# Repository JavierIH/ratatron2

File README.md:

<h1 align="center">Ratatron II</h1>

<p align="center">
  Micromouse robot with four-wheel drive and a suction fan.
</p>

<p align="center">

</p>

> **Work in progress.** The board is being routed and the firmware is waiting for it. The picture is the KiCad 3D
> view, not a photo (yet).

## What's inside

| | |
|---|---|
| **MCU** | STM32F446RET6, Cortex-M4F at 180 MHz |
| **Wall sensors** | 4 IR pairs: SFH4550 emitters and ST-1KL3A phototransistors |
| **IMU** | LSM6DSRX (gyro and accelerometer) over SPI |
| **Drive** | 4 wheels, 2 motors, 2 DRV8874 H-bridges at 20 kHz with current sensing |
| **Encoders** | 2 AS5147P, magnetic, on little boards that snap off the main one |
| **Suction** | a fan driven by a coreless motor, over a hole in the middle of the board |
| **Battery** | 2S LiPo |
| **Interface** | 6 blue LEDs, 2 buttons and a power switch |
| **Connectors** | SWD through a magnetic connector, serial on a header |

## Where things are

- [firmware](firmware/): C on libopencm3, built with PlatformIO (`cd firmware && pio run`, flashed with an ST-Link)
- [hardware](hardware/): KiCad 9 schematic, PCB and custom library
- [mechanics](mechanics/): FreeCAD model (wheels, motor and fan supports)

## Family

- [Ratatron](https://github.com/JavierIH/ratatron), the first one
- [Ratasim](https://github.com/JavierIH/ratasim), the simulator

## Licence

- Firmware: GPLv3 ([LICENSE](LICENSE))
- Electronics: CC BY-SA 4.0 ([hardware/LICENSE](hardware/LICENSE))
- Mechanics: CC BY-SA 4.0 ([mechanics/LICENSE](mechanics/LICENSE))

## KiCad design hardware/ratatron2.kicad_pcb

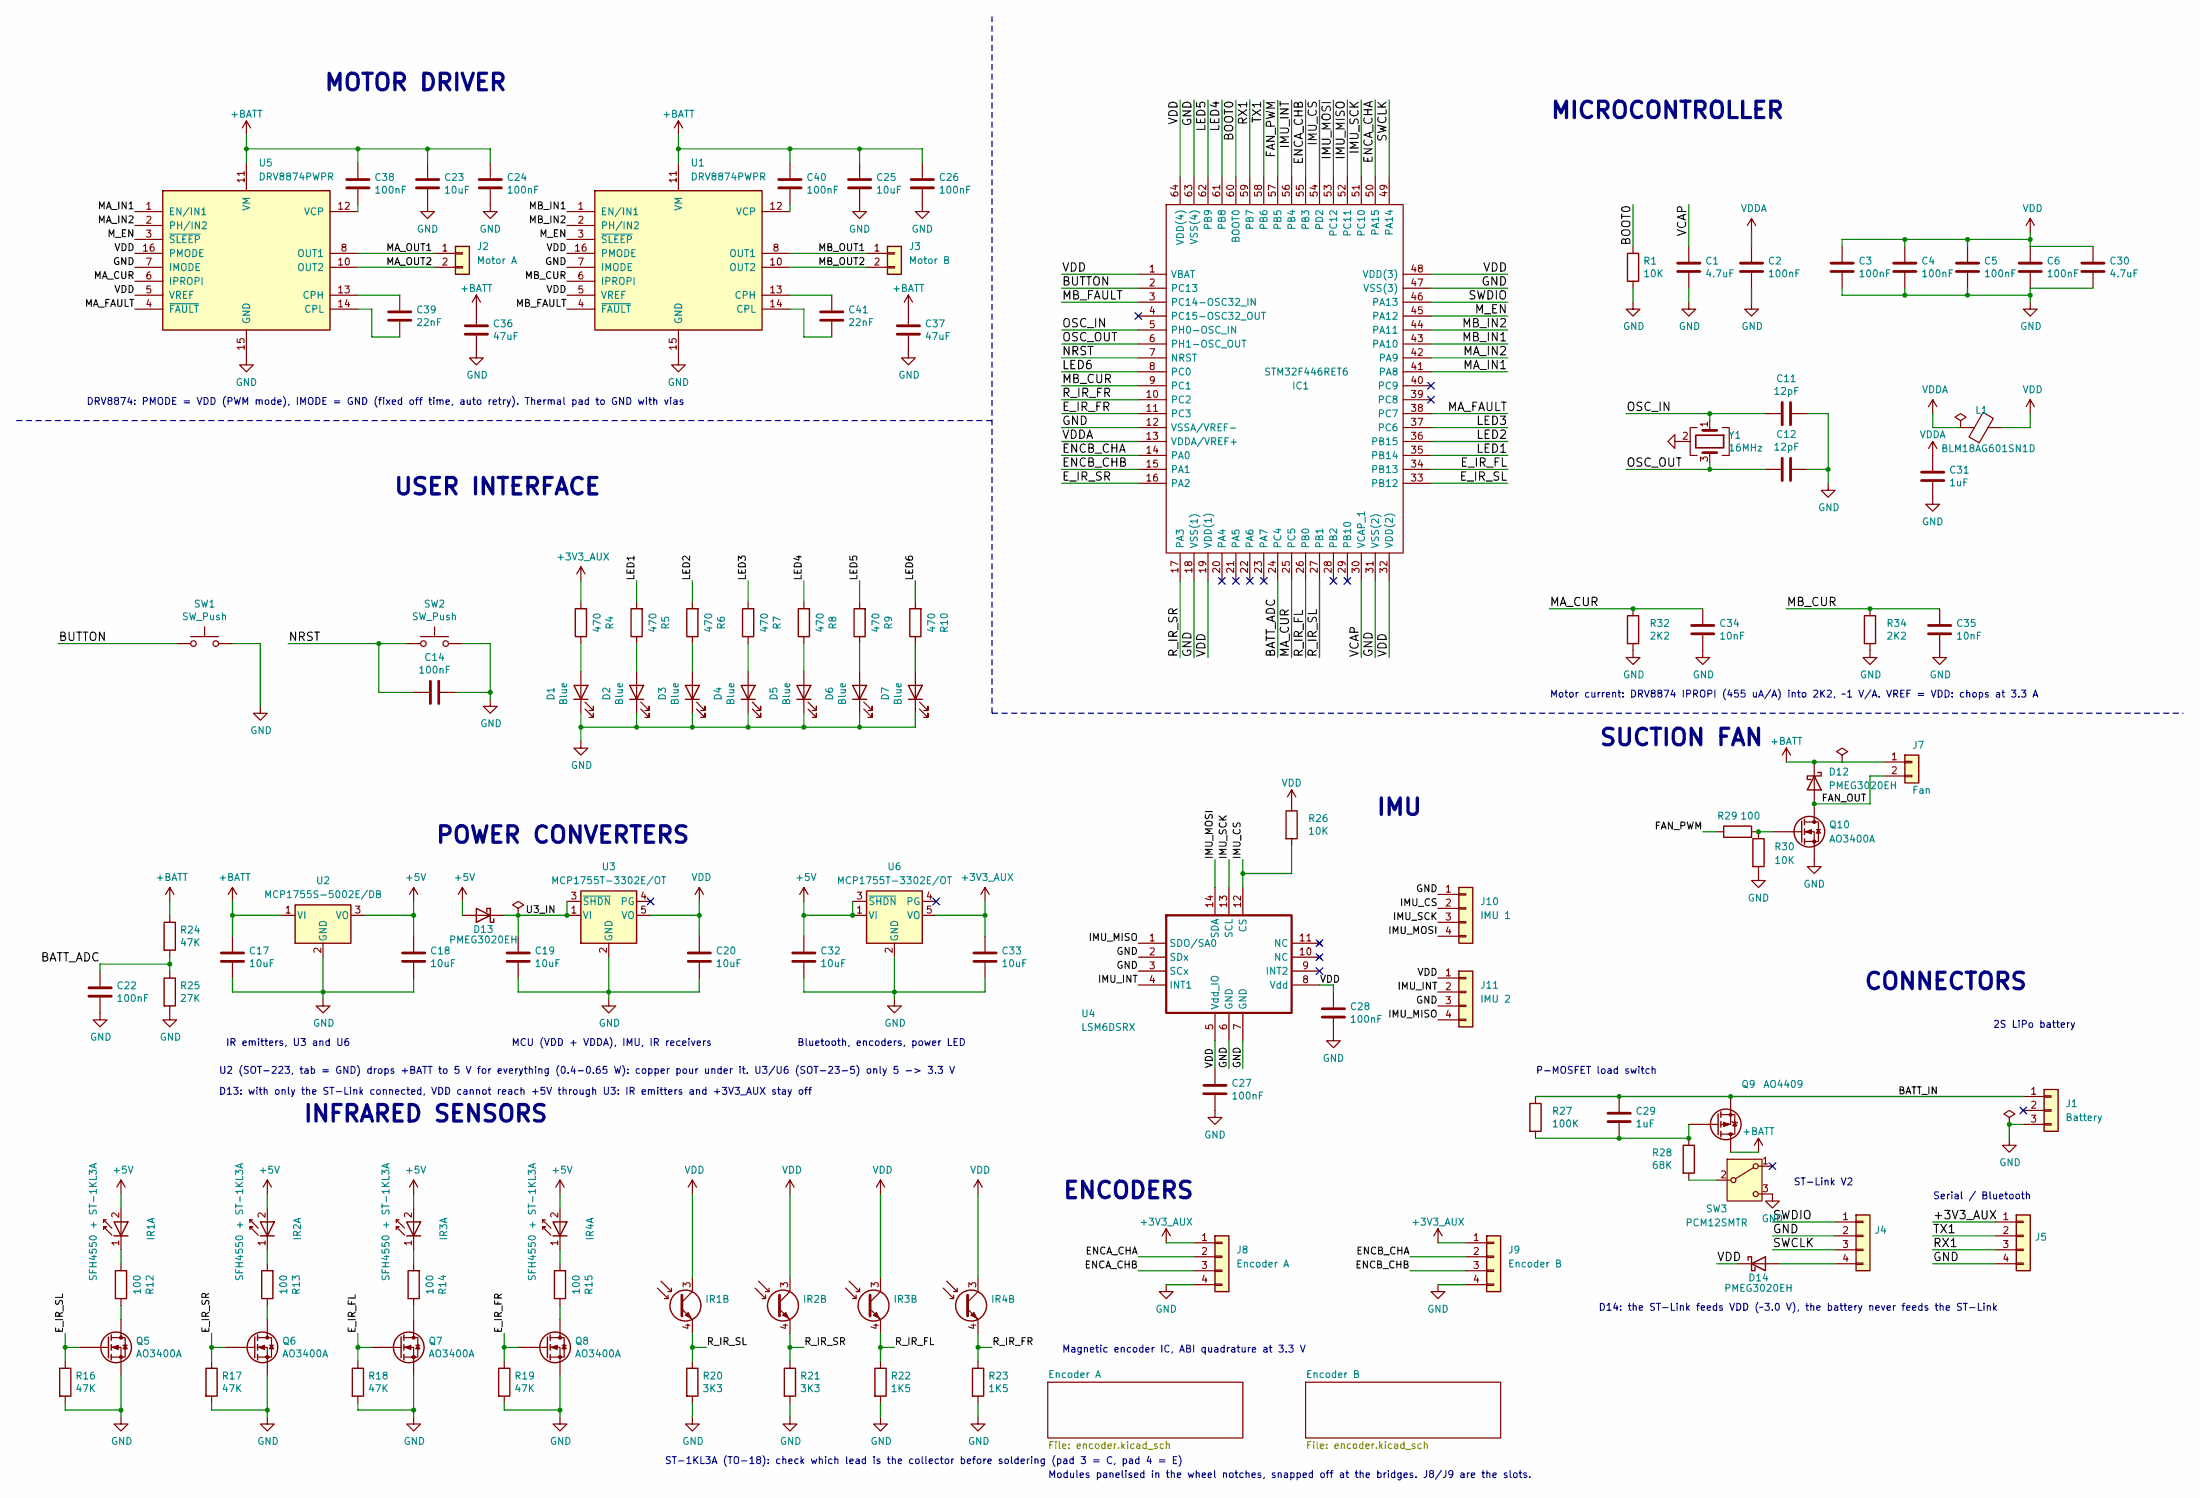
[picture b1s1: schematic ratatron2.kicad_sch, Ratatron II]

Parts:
C1, C30: 4.7uF; R_0603_1608Metric
C2, C3, C4, C5, C6, C14, C22, C24, C26, C27, C28, C38, C40: 100nF; R_0603_1608Metric
C11, C12: 12pF; R_0603_1608Metric
C17, C18, C19, C20, C23, C25, C32, C33: 10uF; R_0603_1608Metric
C29, C31: 1uF; R_0603_1608Metric
C34, C35: 10nF; R_0603_1608Metric
C36, C37: 47uF; C_1206_3216Metric
C39, C41: 22nF; R_0603_1608Metric
D1, D2, D3, D4, D5, D6, D7: Blue; D_0603_1608Metric
D12, D13, D14: PMEG3020EH; D_SOD-123F
IC1: STM32F446RET6; LQFP-64_10x10mm_P0.5mm; Manufacturer_Part_Number STM32F446RET6
IR1, IR3: SFH4550 + ST-1KL3A; IR_PAIR_1x04
IR2, IR4: SFH4550 + ST-1KL3A; IR_PAIR_1x04_R
J1: Battery; JST_XH_B3B-XH-A_1x03_P2.50mm_Vertical
J2: Motor A; SolderPads_1x02_P2.54mm
J3: Motor B; SolderPads_1x02_P2.54mm
J4: SWD; Conn_Magnetic_1x04_P2.54mm_Horizontal
J5: Serial; PinSocket_1x04_P2.54mm_Vertical
J7: Fan; SolderPads_1x02_P2.00mm
J8: Encoder A; Encoder_Slot_1x04
J9: Encoder B; Encoder_Slot_1x04
J10: IMU 1; PinHeader_1x04_P1.27mm_IMU
J11: IMU 2; PinHeader_1x04_P1.27mm_IMU
L1: BLM18AG601SN1D; R_0603_1608Metric
Q5, Q6, Q7, Q8, Q10: AO3400A; SOT-23
Q9: AO4409; SOIC-8_3.9x4.9mm_P1.27mm
R1, R26, R30: 10K; R_0603_1608Metric
R4, R5, R6, R7, R8, R9, R10: 470; R_0603_1608Metric
R12, R13, R14, R15, R29: 100; R_0603_1608Metric
R16, R17, R18, R19, R24: 47K; R_0603_1608Metric
R20, R21: 3K3; R_0603_1608Metric
R22, R23: 1K5; R_0603_1608Metric
R25: 27K; R_0603_1608Metric
R27: 100K; R_0603_1608Metric
R28: 68K; R_0603_1608Metric
R32, R34: 2K2; R_0603_1608Metric
SW1, SW2: SW_Push; SW_Push_1P1T_NO_CK_KMR2
SW3: PCM12SMTR; SW_SPDT_PCM12
U1, U5: DRV8874PWPR; HTSSOP-16-1EP_4.4x5mm_P0.65mm_EP3.4x5mm_Mask2.46x3.55mm
U2: MCP1755S-5002E/DB; SOT-223-3_TabPin2
U3, U6: MCP1755T-3302E/OT; SOT-23-5
U4: LSM6DSRX; Bosch_LGA-14_3x2.5mm_P0.5mm
Y1: 16MHz; Crystal_SMD_3225-4Pin_3.2x2.5mm

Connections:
+3V3_AUX: C33.1, J5.1, J8.1, J9.1, R4.2, U6.5 (VO)
+5V: C18.1, C32.1, D13.2 (A), IR1.2 (A), IR2.2 (A), IR3.2 (A), IR4.2 (A), U2.3 (VO), U6.1 (VI), U6.3 (~SHDN)
+BATT: C17.1, C23.1, C24.1, C25.1, C26.1, C36.1, C37.1, C38.1, C40.1, D12.1 (K), J7.1, Q9.5 (D), Q9.6 (D), Q9.7 (D), Q9.8 (D), R24.1, U1.11 (VM), U2.1 (VI), U5.11 (VM)
/BATT_ADC: C22.1, IC1.24 (PC4), R24.2, R25.1
/BATT_IN: C29.1, J1.1, Q9.1 (S), Q9.2 (S), Q9.3 (S), R27.1
/BOOT0: IC1.60 (BOOT0), R1.1
/BUTTON: IC1.2 (PC13), SW1.1; also elsewhere on the board
/ENCA_CHA: IC1.50 (PA15), J8.2
/ENCA_CHB: IC1.55 (PB3), J8.3
/ENCB_CHA: IC1.14 (PA0), J9.2
/ENCB_CHB: IC1.15 (PA1), J9.3
/E_IR_FL: IC1.34 (PB13), Q7.1 (G), R18.1
/E_IR_FR: IC1.11 (PC3), Q8.1 (G), R19.1
/E_IR_SL: IC1.33 (PB12), Q5.1 (G), R16.1
/E_IR_SR: IC1.16 (PA2), Q6.1 (G), R17.1
/FAN_OUT: D12.2 (A), J7.2, Q10.3 (D)
/FAN_PWM: IC1.57 (PB5), R29.1
/IMU_CS: IC1.54 (PD2), J10.2, R26.2, U4.12 (CS)
/IMU_INT: IC1.56 (PB4), J11.2, U4.4 (INT1)
/IMU_MISO: IC1.52 (PC11), J11.4, U4.1 (SDO/SA0)
/IMU_MOSI: IC1.53 (PC12), J10.4, U4.14 (SDA)
/IMU_SCK: IC1.51 (PC10), J10.3, U4.13 (SCL)
/LED1: IC1.35 (PB14), R5.2
/LED2: IC1.36 (PB15), R6.2
/LED3: IC1.37 (PC6), R7.2
/LED4: IC1.61 (PB8), R8.2
/LED5: IC1.62 (PB9), R9.2
/LED6: IC1.8 (PC0), R10.2
/MA_CUR: C34.1, IC1.25 (PC5), R32.1, U5.6 (IPROPI)
/MA_FAULT: IC1.38 (PC7), U5.4 (~FAULT)
/MA_IN1: IC1.41 (PA8), U5.1 (EN/IN1)
/MA_IN2: IC1.42 (PA9), U5.2 (PH/IN2)
/MA_OUT1: J2.1, U5.8 (OUT1)
/MA_OUT2: J2.2, U5.10 (OUT2)
/MB_CUR: C35.1, IC1.9 (PC1), R34.1, U1.6 (IPROPI)
/MB_FAULT: IC1.3 (PC14-OSC32_IN), U1.4 (~FAULT)
/MB_IN1: IC1.43 (PA10), U1.1 (EN/IN1)
/MB_IN2: IC1.44 (PA11), U1.2 (PH/IN2)
/MB_OUT1: J3.1, U1.8 (OUT1)
/MB_OUT2: J3.2, U1.10 (OUT2)
/M_EN: IC1.45 (PA12), U1.3 (~SLEEP), U5.3 (~SLEEP)
/NRST: C14.2, IC1.7 (NRST), SW2.1; also elsewhere on the board
/OSC_IN: C11.2, IC1.5 (PH0-OSC_IN), Y1.1
/OSC_OUT: C12.2, IC1.6 (PH1-OSC_OUT), Y1.3
/RX1: IC1.59 (PB7), J5.3
/R_IR_FL: IC1.26 (PB0), IR3.4 (E), R22.1
/R_IR_FR: IC1.10 (PC2), IR4.4 (E), R23.1
/R_IR_SL: IC1.27 (PB1), IR1.4 (E), R20.1
/R_IR_SR: IC1.17 (PA3), IR2.4 (E), R21.1
/SWCLK: IC1.49 (PA14), J4.3
/SWDIO: IC1.46 (PA13), J4.1
/TX1: IC1.58 (PB6), J5.2
/U3_IN: C19.1, D13.1 (K), U3.1 (VI), U3.3 (~SHDN)
/VCAP: C1.1, IC1.30 (VCAP_1)
GND: C1.2, C2.2, C3.2, C4.2, C5.2, C6.2, C11.1, C12.1, C14.1, C17.2, C18.2, C19.2, C20.2, C22.2, C23.2, C24.2, C25.2, C26.2, C27.2, C28.2, C30.2, C31.2, C32.2, C33.2, C34.2, C35.2, C36.2, C37.2, D1.1 (K), D2.1 (K), D3.1 (K), D4.1 (K), D5.1 (K), D6.1 (K), D7.1 (K), IC1.12 (VSSA/VREF-), IC1.18 (VSS(1)), IC1.31 (VSS(2)), IC1.47 (VSS(3)), IC1.63 (VSS(4)), J1.3, J4.2, J5.4, J8.4, J9.4, J10.1, J11.3, Q5.2 (S), Q6.2 (S), Q7.2 (S), Q8.2 (S), Q10.2 (S), R1.2, R16.2, R17.2, R18.2, R19.2, R20.2, R21.2, R22.2, R23.2, R25.2, R30.2, R32.2, R34.2, SW1.2, SW2.2, SW3.3 (C), U1.7 (IMODE), U1.9 (PGND), U1.15 (GND), U1.17 (PAD), U2.2 (GND), U3.2 (GND), U4.2 (SDx), U4.3 (SCx), U4.6 (GND), U4.7 (GND), U5.7 (IMODE), U5.9 (PGND), U5.15 (GND), U5.17 (PAD), U6.2 (GND), Y1.2 (G), Y1.4 (G); also elsewhere on the board
unnamed: D1.2 (A), R4.1
unnamed: D2.2 (A), R5.1
unnamed: D3.2 (A), R6.1
unnamed: D4.2 (A), R7.1
unnamed: D5.2 (A), R8.1
unnamed: D6.2 (A), R9.1
unnamed: D7.2 (A), R10.1
unnamed: D14.2 (A), J4.4
unnamed: IR1.1 (K), R12.2
unnamed: IR2.1 (K), R13.2
unnamed: IR3.1 (K), R14.2
unnamed: IR4.1 (K), R15.2
unnamed: Q5.3 (D), R12.1
unnamed: Q6.3 (D), R13.1
unnamed: Q7.3 (D), R14.1
unnamed: Q8.3 (D), R15.1
unnamed: C29.2, Q9.4 (G), R27.2, R28.1
unnamed: Q10.1 (G), R29.2, R30.1
unnamed: R28.2, SW3.2 (B)
unnamed: C41.1, U1.13 (CPH)
unnamed: C41.2, U1.14 (CPL)
unnamed: C40.2, U1.12 (VCP)
unnamed: C39.1, U5.13 (CPH)
unnamed: C39.2, U5.14 (CPL)
unnamed: C38.2, U5.12 (VCP)
VDD: C3.1, C4.1, C5.1, C6.1, C20.1, C27.1, C28.1, C30.1, D14.1 (K), IC1.1 (VBAT), IC1.19 (VDD(1)), IC1.32 (VDD(2)), IC1.48 (VDD(3)), IC1.64 (VDD(4)), IR1.3 (C), IR2.3 (C), IR3.3 (C), IR4.3 (C), J11.1, L1.2, R26.1, U1.5 (VREF), U1.16 (PMODE), U3.5 (VO), U4.5 (Vdd_IO), U4.8 (Vdd), U5.5 (VREF), U5.16 (PMODE)
VDDA: C2.1, C31.1, IC1.13 (VDDA/VREF+), L1.1

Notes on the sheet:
Motor current: DRV8874 IPROPI (455 uA/A) into 2K2, ~1 V/A. VREF = VDD: chops at 3.3 A
ST-1KL3A (TO-18): check which lead is the collector before soldering (pad 3 = C, pad 4 = E)
Magnetic encoder IC, ABI quadrature at 3.3 V
POWER CONVERTERS
DRV8874: PMODE = VDD (PWM mode), IMODE = GND (fixed off time, auto retry). Thermal pad to GND with vias
P-MOSFET load switch
ENCODERS
MOTOR DRIVER
SUCTION FAN
D14: the ST-Link feeds VDD (~3.0 V), the battery never feeds the ST-Link
ST-Link V2
USER INTERFACE
IMU
MCU (VDD + VDDA), IMU, IR receivers
U2 (SOT-223, tab = GND) drops +BATT to 5 V for everything (0.4-0.65 W): copper pour under it. U3/U6 (SOT-23-5) only 5 -> 3.3 V
Serial / Bluetooth
IR emitters, U3 and U6
INFRARED SENSORS
Bluetooth, encoders, power LED
D13: with only the ST-Link connected, VDD cannot reach +5V through U3: IR emitters and +3V3_AUX stay off
2S LiPo battery
MICROCONTROLLER
CONNECTORS
Modules panelised in the wheel notches, snapped off at the bridges. J8/J9 are the slots.

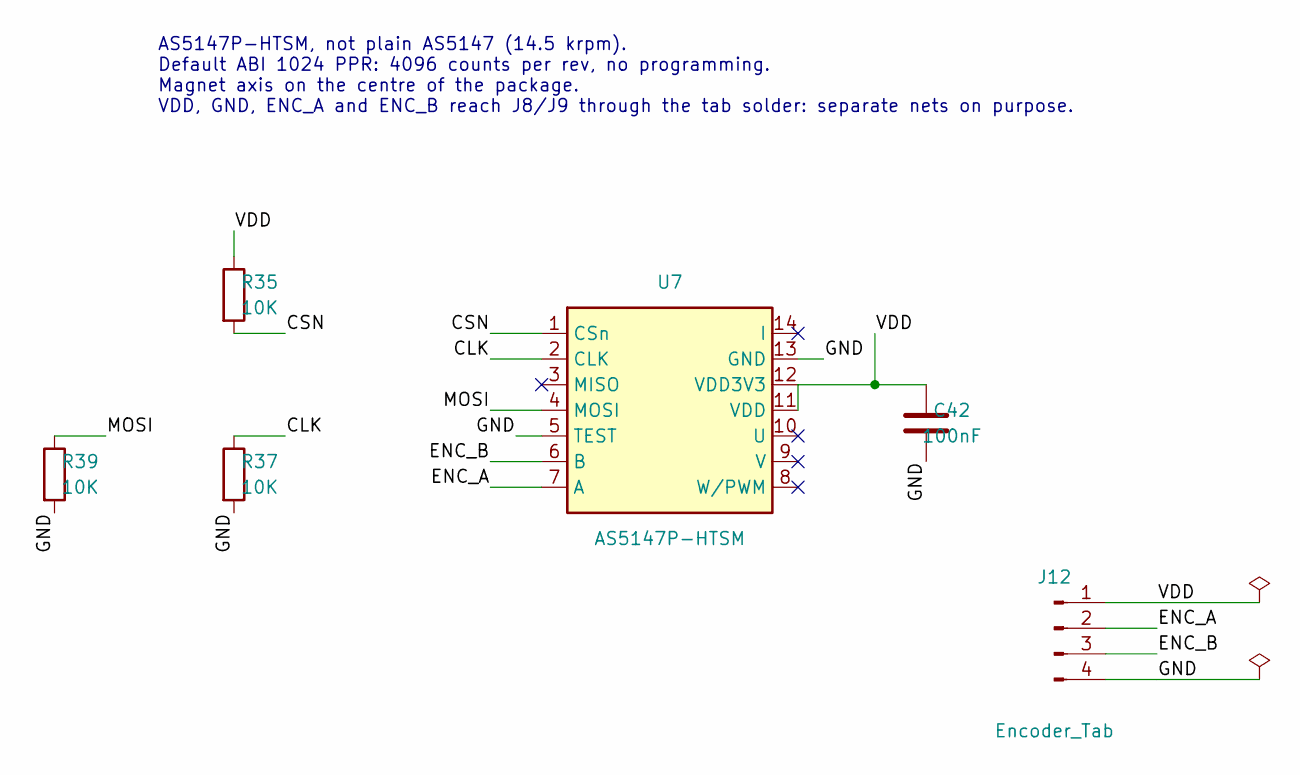
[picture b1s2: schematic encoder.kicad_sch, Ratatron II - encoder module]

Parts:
C42: 100nF; R_0603_1608Metric
J12: Encoder_Tab; Encoder_Tab_1x04
R35, R37, R39: 10K; R_0603_1608Metric
U7: AS5147P-HTSM; TSSOP-14_4.4x5mm_P0.65mm

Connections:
/Encoder A/CLK: R37.1, U7.2 (CLK)
/Encoder A/CSN: R35.2, U7.1 (CSn)
/Encoder A/ENC_A: J12.2, U7.7 (A)
/Encoder A/ENC_B: J12.3, U7.6 (B)
/Encoder A/GND: C42.2, J12.4, R37.2, R39.2, U7.5 (TEST), U7.13 (GND)
/Encoder A/MOSI: R39.1, U7.4 (MOSI)
/Encoder A/VDD: C42.1, J12.1, R35.1, U7.11 (VDD), U7.12 (VDD3V3)

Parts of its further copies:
C43: 100nF; R_0603_1608Metric
J13: Encoder_Tab; Encoder_Tab_1x04
R36, R38, R40: 10K; R_0603_1608Metric
U8: AS5147P-HTSM; TSSOP-14_4.4x5mm_P0.65mm

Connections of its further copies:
/Encoder B/CLK: R38.1, U8.2 (CLK)
/Encoder B/CSN: R36.2, U8.1 (CSn)
/Encoder B/ENC_A: J13.2, U8.7 (A)
/Encoder B/ENC_B: J13.3, U8.6 (B)
/Encoder B/GND: C43.2, J13.4, R38.2, R40.2, U8.5 (TEST), U8.13 (GND)
/Encoder B/MOSI: R40.1, U8.4 (MOSI)
/Encoder B/VDD: C43.1, J13.1, R36.1, U8.11 (VDD), U8.12 (VDD3V3)

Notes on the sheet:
AS5147P-HTSM, not plain AS5147 (14.5 krpm). Default ABI 1024 PPR: 4096 counts per rev, no programming. Magnet axis on the centre of the package. VDD, GND, ENC_A and ENC_B reach J8/J9 through the tab solder: separate nets on purpose.

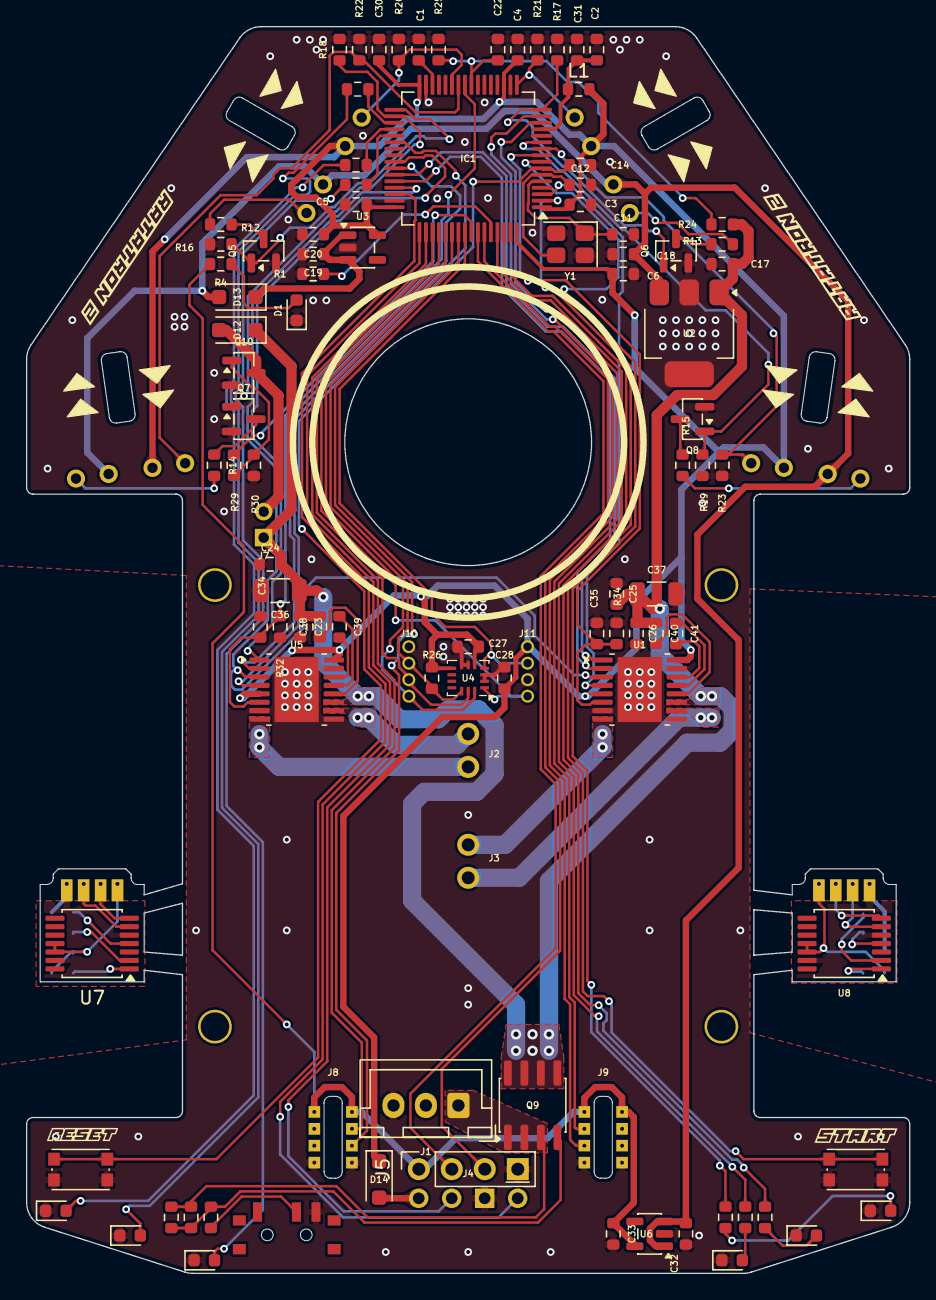
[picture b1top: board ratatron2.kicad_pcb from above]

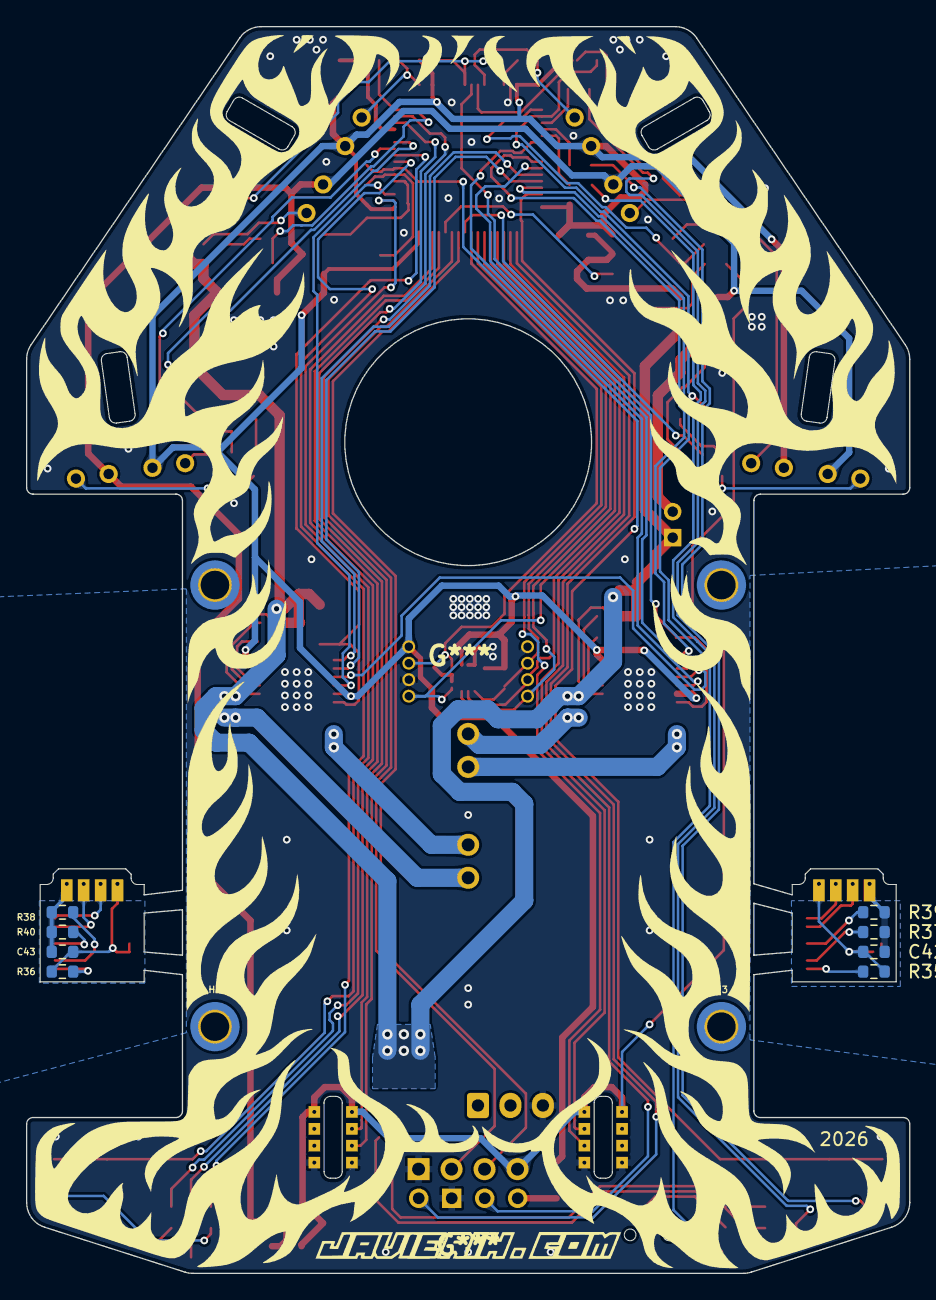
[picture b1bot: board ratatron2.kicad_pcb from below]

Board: 2 copper layers, 68.0 x 96.0 mm, 121 parts (13 on the bottom side), 94 nets.

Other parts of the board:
H1, H2, H3, H4: MountingHole_2.2mm_M2_ISO14580_Pad_TopOnly
MECH1: Drivetrain
RESET: SW_Push; SW_Push_1P1T_NO_CK_KMR2
SELECT: SW_Push; SW_Push_1P1T_NO_CK_KMR2

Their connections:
/BUTTON: SELECT.1; also elsewhere on the board
/NRST: RESET.1; also elsewhere on the board
GND: RESET.2, SELECT.2; also elsewhere on the board

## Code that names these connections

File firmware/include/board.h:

#ifndef BOARD_H
#define BOARD_H

#include <libopencm3/stm32/gpio.h>
#include <libopencm3/stm32/adc.h>

// Ratatron II pinout (STM32F446RET6, LQFP64)
// Net names match hardware/ratatron2.kicad_sch. Pin = LQFP64 package pin.
// IC1 sits at rot 180 in the nose: pins 17-32 face the front edge, 33-48 the
// left IR, 49-64 the fan (rear) and 1-16 the right IR.
//
//  Pin  Port  Net        Function
//   2   PC13  BUTTON     in, internal pull-up, active low
//   3   PC14  MB_FAULT   in, nFAULT of U1
//   5   PH0   OSC_IN     16MHz HSE
//   6   PH1   OSC_OUT
//   8   PC0   LED6       out
//   9   PC1   MB_CUR     ADC123_IN11, IPROPI of U1 (motor B current)
//  10   PC2   R_IR_FR    ADC123_IN12
//  11   PC3   E_IR_FR    out
//  14   PA0   ENCB_CHA   TIM5_CH1 AF2 (32 bit timer)
//  15   PA1   ENCB_CHB   TIM5_CH2 AF2
//  16   PA2   E_IR_SR    out
//  17   PA3   R_IR_SR    ADC123_IN3
//  24   PC4   BATT_ADC   ADC12_IN14
//  25   PC5   MA_CUR     ADC12_IN15, IPROPI of U5 (motor A current)
//  26   PB0   R_IR_FL    ADC12_IN8
//  27   PB1   R_IR_SL    ADC12_IN9
//  33   PB12  E_IR_SL    out
//  34   PB13  E_IR_FL    out
//  35   PB14  LED1       out
//  36   PB15  LED2       out
//  37   PC6   LED3       out
//  38   PC7   MA_FAULT   in, nFAULT of U5
//  41   PA8   MA_IN1     TIM1_CH1 AF1
//  42   PA9   MA_IN2     TIM1_CH2 AF1
//  43   PA10  MB_IN1     TIM1_CH3 AF1
//  44   PA11  MB_IN2     TIM1_CH4 AF1
//  45   PA12  M_EN       out, nSLEEP of both DRV8874
//  46   PA13  SWDIO      J4
//  49   PA14  SWCLK      J4
//  50   PA15  ENCA_CHA   TIM2_CH1 AF1 (32 bit timer)
//  51   PC10  IMU_SCK    SPI3_SCK AF6
//  52   PC11  IMU_MISO   SPI3_MISO AF6
//  53   PC12  IMU_MOSI   SPI3_MOSI AF6
//  54   PD2   IMU_CS     out
//  55   PB3   ENCA_CHB   TIM2_CH2 AF1
//  56   PB4   IMU_INT    in (EXTI4), LSM6DSRX INT1
//  57   PB5   FAN_PWM    TIM3_CH2 AF2
//  58   PB6   TX1        USART1_TX AF7 -> J5
//  59   PB7   RX1        USART1_RX AF7 -> J5
//  61   PB8   LED4       out
//  62   PB9   LED5       out
//
//  Not connected: PC15, PA4, PA5, PA6, PA7, PB2, PB10, PC8, PC9
//  Reserved: PC9 buzzer (TIM8_CH4)

struct pin {
    uint32_t port;
    uint16_t pin;
};

// Serial
#define SERIAL_PORT         GPIOB
#define SERIAL_PINS         (GPIO6 | GPIO7)

// User interface
#define BUTTON_PORT         GPIOC
#define BUTTON_PIN          GPIO13
#define NUM_LEDS            6
#define LED_PINS            {{GPIOB, GPIO14}, {GPIOB, GPIO15}, {GPIOC, GPIO6}, \
                             {GPIOB, GPIO8}, {GPIOB, GPIO9}, {GPIOC, GPIO0}}

// Battery: R24 47K / R25 27K
#define BATT_PORT           GPIOC
#define BATT_PIN            GPIO4
#define BATT_CHANNEL        ADC_CHANNEL14
#define BATT_R_TOP          47
#define BATT_R_BOTTOM       27

// Motor drivers: 2x DRV8874 in PWM mode (PMODE = VDD), PWM on IN1/IN2
#define MOTOR_PWM_PORT      GPIOA
#define MOTOR_PWM_PINS      (GPIO8 | GPIO9 | GPIO10 | GPIO11)
#define MOTOR_EN_PORT       GPIOA
#define MOTOR_EN_PIN        GPIO12
#define MOTOR_FAULT_PORT    GPIOC
#define MA_FAULT_PIN        GPIO7
#define MB_FAULT_PIN        GPIO14
#define MOTOR_PWM_FREQ      20000

// Motor current: IPROPI (455uA per A of low side current) into 2K2 to GND,
// 0V at 0A, ~1V/A, 10nF filter. VREF = VDD, so each driver chops above ~3.3A
#define MOTOR_CUR_PORT      GPIOC
#define MOTOR_CUR_PINS      (GPIO5 | GPIO1)
#define MA_CUR_CHANNEL      ADC_CHANNEL15
#define MB_CUR_CHANNEL      ADC_CHANNEL11
#define MOTOR_CUR_UA_PER_A  455     // IPROPI current per A of motor current
#define MOTOR_CUR_R_OHM     2200    // R32, R34

// Suction fan: Q10 driven by TIM3_CH2
#define FAN_PORT            GPIOB
#define FAN_PIN             GPIO5
#define FAN_PWM_FREQ        20000

// Encoders: A on TIM2 (channels on two ports), B on TIM5
#define ENCA_CHA_PORT       GPIOA
#define ENCA_CHA_PIN        GPIO15
#define ENCA_CHB_PORT       GPIOB
#define ENCA_CHB_PIN        GPIO3
#define ENCB_PORT           GPIOA
#define ENCB_PINS           (GPIO0 | GPIO1)

// IMU LSM6DSRX on SPI3
#define IMU_SPI_PORT        GPIOC
#define IMU_SPI_PINS        (GPIO10 | GPIO11 | GPIO12)
#define IMU_CS_PORT         GPIOD
#define IMU_CS_PIN          GPIO2
#define IMU_INT_PORT        GPIOB
#define IMU_INT_PIN         GPIO4

// Infrared sensors: emitters through Q5..Q8, receivers on ADC
#define E_IR_SL             {GPIOB, GPIO12}
#define E_IR_SR             {GPIOA, GPIO2}
#define E_IR_FL             {GPIOB, GPIO13}
#define E_IR_FR             {GPIOC, GPIO3}
#define R_IR_SL             {GPIOB, GPIO1}
#define R_IR_SR             {GPIOA, GPIO3}
#define R_IR_FL             {GPIOB, GPIO0}
#define R_IR_FR             {GPIOC, GPIO2}
#define R_IR_SL_CHANNEL     ADC_CHANNEL9
#define R_IR_SR_CHANNEL     ADC_CHANNEL3
#define R_IR_FL_CHANNEL     ADC_CHANNEL8
#define R_IR_FR_CHANNEL     ADC_CHANNEL12

#endif

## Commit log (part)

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2019-12-29 first draft
2019-12-29 added edge cut from dxf
2024-11-05 new everything

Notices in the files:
README.md:
Code: GPLv3
Hardware: CC BY-SA 4.0
